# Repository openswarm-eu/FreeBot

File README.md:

# FreeBot
Contains FreeBot files and source code.
The Hardware folder contains schematics for the various versions of the FreeBot board and associated evaluation boards.
The software folder contains the FreeBot subfolder, which contains the core functionality of FreeBot and reference implementation of the library for BLE control. 
The repository will keep being updated with designs for both hardware and software.

# Hardware revisions

| Version        | SoC      | Feather-header | Picture                                       |
|:--------------:|:--------:|:--------------:|:---------------------------------------------:|
| [v1.0a](#v10a) | nrf52840 | &cross;        ||
| [v1.1a](#v11a) | nrf52840 | &cross;        ||
| [v1.1b](#v11b) | nrf52840 | &check;        ||

## v1.0a

CapBot v1.0 has a physical switch (`SW4`) to cut the UART lines from the DAP-link on-board debugger.
This switch should be enabled when printing to a serial terminal over USB.

Furthermore, another physical switch (`SW3`) cuts the SWD lines used for programming the &micro;Processor.
This switch should be enabled in order to flash.

## v1.1a

Nothing special (yet).

## v1.1b

> [!WARNING]
> The pins `IO1`, `IO2` and `IO3` on the feather-header correspond with `D15`, `D16` and `SW2` respectively.
> Make sure that these are not shorted accidentally because of this.
> 

# Acknowledgement

Part of the source code in this repository is developed within the frame and for the purpose of the OpenSwarm project. This project has received funding from the European Unioan's Horizon Europe Framework Programme under Grant Agreement No. 101093046.

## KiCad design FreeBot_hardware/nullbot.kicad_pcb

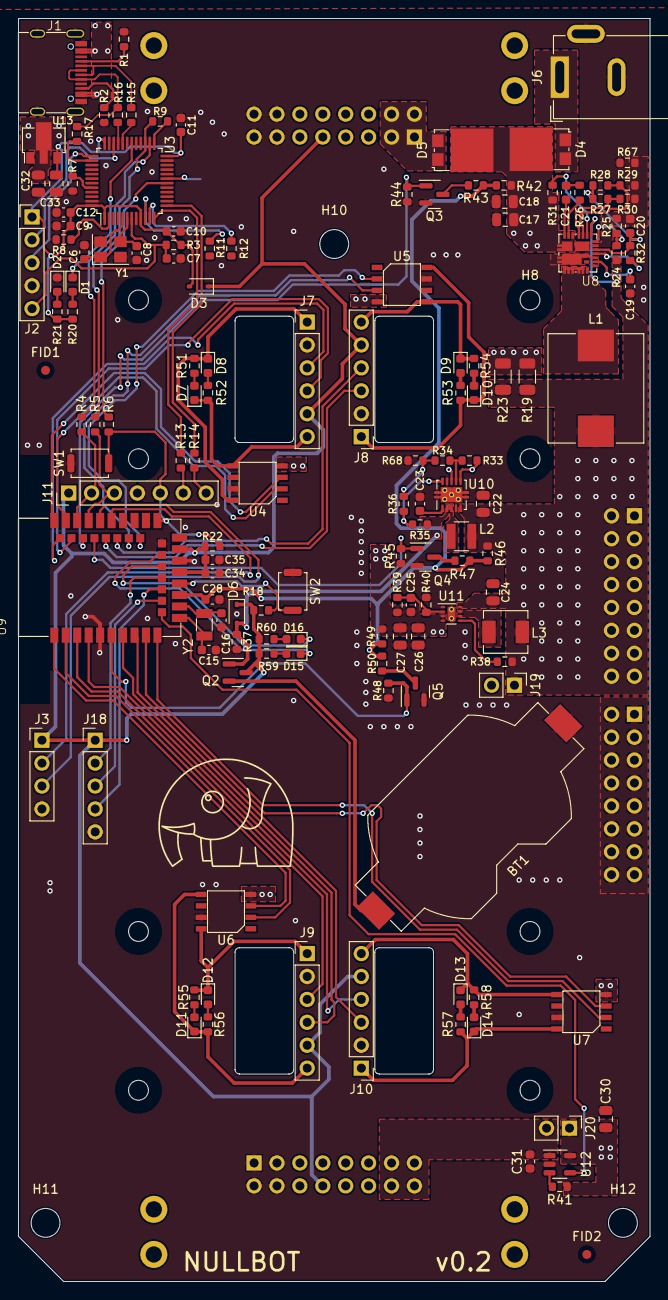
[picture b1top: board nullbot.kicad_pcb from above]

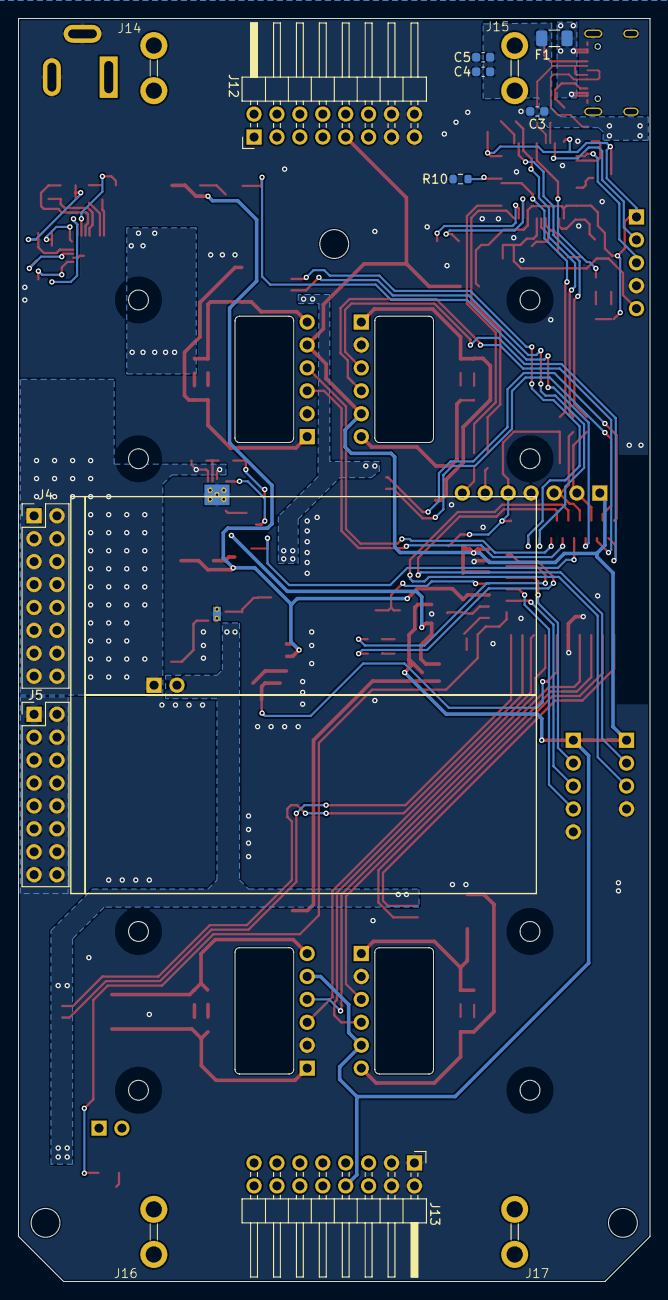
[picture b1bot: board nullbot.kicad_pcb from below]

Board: 2 copper layers, 70.0 x 140.0 mm, 165 parts (13 on the bottom side), 116 nets.

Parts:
BT1: Battery_Cell; BatteryHolder_Keystone_1058_1x2032
C3, C4, C5, C20: 1uF; C_0603_1608Metric
C6, C8: 22p; C_0603_1608Metric
C7, C9, C10, C11, C12: 100n; C_0603_1608Metric
C15, C16: 12pF; C_0603_1608Metric
C17, C18, C26, C27: 22uF; C_0805_2012Metric
C19: 2.2uF; C_0603_1608Metric
C21, C23, C31, C34, C35: 0.1uF; C_0603_1608Metric
C22, C24, C30, C32, C33: 10uF; C_0805_2012Metric
C25: 10pF; C_0603_1608Metric
C28: 0.01uF; C_0603_1608Metric
D1: Red; LED_0603_1608Metric
D2: Green; LED_0603_1608Metric
D3, D6: CUS10S30,H3F; D_SOD-323
D4, D5: 10S45SP; TO-277A
D7, D10, D11, D14: GREEN LED NCD0603G1; LED_0603_1608Metric
D8, D9, D12, D13: RED LED NCD0603R1; LED_0603_1608Metric
D15, D16: 19-217/BHC-ZL1M2RY/3T; LED_0603_1608Metric
F1: S1206-F-6.0A; Fuse_1206_3216Metric
FID1, FID2: Fiducial; Fiducial_1mm_Mask2mm
H1, H2, H3, H4, H5, H6, H7, H8: MountingHole; MountingHole_2.2mm_M2_ISO7380
H10, H11, H12: MountingHole; MountingHole_3.2mm_M3_ISO14580
J1: USB-type-c-16p; TYPE-C-31-M-12
J2, J18: Conn_01x05; PinHeader_1x05_P2.54mm_Vertical
J3: Conn_01x04; PinHeader_1x04_P2.54mm_Vertical
J4, J5: Conn_02x08_Counter_Clockwise; PinHeader_2x08_P2.54mm_Vertical
J6: Barrel_Jack_MountingPin; BarrelJack_GCT_DCJ200-10-A_Horizontal
J7, J8, J9, J10: Conn_01x06; PinHeader_1x06_P2.54mm_Vertical
J11: Conn_01x07; PinHeader_1x07_P2.54mm_Vertical
J12, J13: Conn_02x08_Odd_Even; PinHeader_2x08_P2.54mm_Horizontal
J14, J17: Conn_01x01; M3-side-terminal-DZ-32
J15, J16: Conn_01x01; M3-side-terminal-DZ-43
J19, J20: Conn_01x02; PinHeader_1x02_P2.54mm_Vertical
L1: 300nH; L_Chilisin_BMRF00101040
L2: 2.2uH SWPA3015S2R2MT; L_Abracon_ASPI-3012S
L3: 470nH FXL0420-R47-M; L_Sunlord_MWSA0412S
Q2: SSM3J332R; SOT-23
Q3, Q4, Q5: 2N7002; SOT-23
R1, R2: 5.1k; R_0603_1608Metric
R3, R7, R18, R22, R27, R31, R32, R38, R40, R41, R44, R45, R48: 100k; R_0603_1608Metric
R4, R5, R6, R11, R12, R13, R14, R15, R16: 22; R_0603_1608Metric
R8: 10k DNP; R_0603_1608Metric
R9, R20, R52, R53, R56, R57, R59, R60: 100; R_0603_1608Metric
R10, R68: 0; R_0603_1608Metric
R17: 1.5k; R_0603_1608Metric
R19, R23: DNP; R_1206_3216Metric
R21, R51, R54, R55, R58: 27; R_0603_1608Metric
R24: 36.5k; R_0603_1608Metric
R25, R34, R43, R47, R50: 10k; R_0603_1608Metric
R26, R67: 1; R_0603_1608Metric
R28: 499k; R_0603_1608Metric
R29, R30: DNP; R_0603_1608Metric
R33: 34.8k; R_0603_1608Metric
R35, R37: 1M; R_0603_1608Metric
R36: 180k; R_0603_1608Metric
R39: 316k; R_0603_1608Metric
R42, R46, R49: 390k; R_0603_1608Metric
SW1, SW2: TS-1088-AR02016; SW_Push_SPST_NO_Alps_SKRK
U3: STM32F103CBTx; LQFP-48_7x7mm_P0.5mm
U4, U5, U6, U7: BDR6120H; motor-driver-BDR6120H
U8: SIC431AED-T1-GE3; MLP44-24L SiC431
U9: E73-2G4M08S1C
U10: TPS61201DRC; Texas_S-PVSON-N10_ThermalVias
U11: WSON-8-1EP_2x2mm_P0.5mm_EP0.9x1.6mm_ThermalVias
U12: RT9742AGJ5F; TSOT-23-5
U13: HT7533-1; SOT-89-3
Y1: Crystal_GND24; Crystal_SMD_3225-4Pin_3.2x2.5mm
Y2: Q13FC1350000400; Crystal_SMD_3215-2Pin_3.2x1.5mm

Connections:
/USB-VDD: C9.1, C10.1, C11.1, C12.1, C33.1, D3.2 (A), J2.1, R3.2, R20.1, R21.1, U3.1 (VBAT), U3.9 (VDDA), U3.24 (VDD), U3.36 (VDD), U3.48 (VDD), U13.3 (VOUT)
/Vbotin: D5.1 (A), D5.2 (A), J12.1, J12.2, J12.3, J12.4
/Vbotout: C31.2, J13.13, J13.14, J13.15, J13.16, J20.2, U12.1 (VOUT)
/Vmotor: C25.2, C26.1, C27.1, C30.1, J19.2, J20.1, R39.1, R41.1, R49.1, U4.4 (VDD), U5.4 (VDD), U6.4 (VDD), U7.4 (VDD), U11.3 (VOUT), U11.4 (VOUT), U12.5 (VIN)
/daplink/dap-inner-usb_N: R15.2, U3.32 (PA11)
/daplink/dap-inner-usb_P: R16.2, U3.33 (PA12)
/daplink/dap-led-red: D1.1 (K), U3.30 (PA9)
/daplink/dap-nrst: C7.1, J2.5, R3.1, U3.7 (NRST)
/daplink/dap-swclk: J2.3, U3.37 (PA14)
/daplink/dap-swdio: J2.2, U3.34 (PA13)
/daplink/dap-usbd_N: J1.A7 (DN1), J1.B7 (DN2), R15.1
/daplink/dap-usbd_P: J1.A6 (DP1), J1.B6 (DP2), R16.1, R17.2
/daplink/tgt-swd.clk: J11.2, R4.1, U9.39 (SWDCLK)
/daplink/tgt-swd.io: J11.3, R5.1, U9.37 (SWDIO)
/daplink/tgt-swd.rst: J11.5, R6.1, R22.2, SW1.2, U9.26 (P0.18/RESET)
/daplink/tgt-uart.rx: J11.7, R14.2
/daplink/tgt-uart.tx: J11.6, R13.2
/mcu/V-mea: C28.1, R42.2, R43.1, R46.2, R47.1, R49.2, R50.1, U9.15 (P0.05/AIN3)
/mcu/Vbotout-EN: U9.12 (P0.26), U12.4 (EN)
/mcu/Vcap-mea-en: Q4.1 (G), R45.1, U9.36 (P1.00/SWO)
/mcu/Vin-mea-en: Q3.1 (G), R44.1, U9.38 (P1.02-LS)
/mcu/Vmotor-mea-en: Q5.1 (G), R48.1, U9.6 (P1.13-LS)
/mcu/m1-ctrl.in-a: U4.2 (INA), U9.41 (P0.09/NFC1-LS)
/mcu/m1-ctrl.in-b: U4.3 (INB), U9.43 (P0.10/NFC2-LS)
/mcu/m1-hall.c1: J7.4, U9.40 (P1.04-LS)
/mcu/m1-hall.c2: J7.3, U9.42 (P1.06-LS)
/mcu/m2-ctrl.in-a: U5.2 (INA), U9.28 (P0.15)
/mcu/m2-ctrl.in-b: U5.3 (INB), U9.30 (P0.17)
/mcu/m2-hall.c1: J8.4, U9.32 (P0.20)
/mcu/m2-hall.c2: J8.3, U9.34 (P0.22)
/mcu/m3-ctrl.in-a: U6.2 (INA), U9.2 (P1.10-LS)
/mcu/m3-ctrl.in-b: U6.3 (INB), U9.1 (P1.11-LS)
/mcu/m3-hall.c1: J9.4, U9.7 (P0.02/AIN1-LS)
/mcu/m3-hall.c2: J9.3, U9.3 (P0.03/AIN1-LS)
/mcu/m4-ctrl.in-a: U7.2 (INA), U9.10 (P0.30/AIN6-LS)
/mcu/m4-ctrl.in-b: U7.3 (INB), U9.9 (P0.31/AIN7-LS)
/mcu/m4-hall.c1: J10.4, U9.4 (P0.28/AIN4-LS)
/mcu/m4-hall.c2: J10.3, U9.8 (P0.29/AIN5-LS)
/mcu/nrf-led1: D15.1 (K), U9.22 (P0.07)
/mcu/nrf-led2: D16.1 (K), U9.20 (P0.12)
/mcu/nrf-sw: R18.2, SW2.2, U9.17 (P1.09)
/mcu/peri-i2c.scl: J3.3, U9.35 (P0.24)
/mcu/peri-i2c.sda: J3.2, U9.33 (P0.13)
/mcu/peri-spi.miso: J18.4, U9.16 (P0.08)
/mcu/peri-spi.mosi: J18.2, U9.18 (P0.04/AIN2)
/mcu/peri-spi.sck: J18.3, U9.14 (P0.06)
/pwr1/Vcap: C22.1, C24.1, J4.1, J4.2, J4.3, J4.4, J4.5, J4.6, J4.7, J4.8, J4.9, J4.10, J4.11, J4.12, J4.13, J4.14, J4.15, J4.16, J19.1, L1.2, L2.1, L3.1, R19.2, R23.2, R24.1, R33.1, R38.1, R46.1, U8.18 (Vout), U10.5 (VIN), U10.6 (EN), U10.8 (PS), U11.8 (VIN)
/pwr1/buck_en: R31.2, U8.19 (EN)
/pwr2/Vbotout-overcurr: R41.2, U12.3 (~FLG)
/pwr2/Vcap_reg: D6.2 (A), Q2.1 (G), R35.1, R37.1, U10.2 (VOUT)
/pwr2/Vmotor-EN: R38.2, U11.5 (EN)
GND: BT1.2 (-), C3.2, C4.2, C5.2, C6.2, C7.2, C8.2, C9.2, C10.2, C11.2, C12.2, C15.2, C16.2, C17.2, C18.2, C19.2, C20.2, C22.2, C23.1, C24.2, C26.2, C27.2, C28.2, C30.2, C31.1, C32.2, C33.2, C34.2, C35.2, D2.1 (K), J1.0 (SH), J1.1 (SH), J1.2 (SH), J1.3 (SH), J1.A1 (GND), J1.A12 (GND), J1.B1 (GND), J1.B12 (GND), J2.4, J3.4, J5.1, J5.2, J5.3, J5.4, J5.5, J5.6, J5.7, J5.8, J5.9, J5.10, J5.11, J5.12, J5.13, J5.14, J5.15, J5.16, J6.2, J6.3 (MP), J7.2, J8.2, J9.2, J10.2, J11.4, J12.13, J12.14, J12.15, J12.16, J13.1, J13.2, J13.3, J13.4, J18.5, Q3.2 (S), Q4.2 (S), Q5.2 (S), R1.2, R2.2, R7.2, R8.1, R10.1, R25.2, R29.2, R30.2, R37.2, R40.2, R44.2, R45.2, R48.2, R67.1, R67.2, R68.2, SW1.1, SW2.1, U3.8 (VSSA), U3.23 (VSS), U3.35 (VSS), U3.47 (VSS), U4.7 (GND), U5.7 (GND), U6.7 (GND), U7.7 (GND), U8.3 (Pgnd), U8.4 (Pgnd), U8.13 (Pgnd), U8.16 (Agnd), U8.25 (Agnd), U8.27 (Pgnd), U9.5 (GND), U9.21 (GND), U9.24 (GND), U10.4 (PGND), U10.9 (GND), U10.11 (PAD), U11.1 (AGND), U11.9 (PGND), U12.2 (GND), U13.1 (GND), Y1.2, Y1.4
unnamed: BT1.1 (+), Q2.2 (S)
unnamed: C21.2, R26.2
unnamed: D1.2 (A), R20.2
unnamed: D2.2 (A), R21.2
unnamed: D4.1 (A), D4.2 (A), J6.1
unnamed: C17.1, C18.1, D4.3 (K), D5.3 (K), R19.1, R23.1, R31.1, R42.1, U8.1 (Vin), U8.2 (Vin), U8.22 (Vin), U8.26 (Vin)
unnamed: D7.2 (A), R51.2
unnamed: D7.1 (K), J7.6, R52.2, U4.5 (OUTB)
unnamed: D8.2 (A), R52.1
unnamed: D8.1 (K), J7.1, R51.1, U4.8 (OUTA)
unnamed: D9.2 (A), R53.2
unnamed: D9.1 (K), J8.6, R54.2, U5.5 (OUTB)
unnamed: D10.2 (A), R54.1
unnamed: D10.1 (K), J8.1, R53.1, U5.8 (OUTA)
unnamed: D11.2 (A), R55.2
unnamed: D11.1 (K), J9.6, R56.2, U6.5 (OUTB)
unnamed: D12.2 (A), R56.1
unnamed: D12.1 (K), J9.1, R55.1, U6.8 (OUTA)
unnamed: D13.2 (A), R57.2
unnamed: D13.1 (K), J10.6, R58.2, U7.5 (OUTB)
unnamed: D14.2 (A), R58.1
unnamed: D14.1 (K), J10.1, R57.1, U7.8 (OUTA)
unnamed: D15.2 (A), R59.2
unnamed: D16.2 (A), R60.2
unnamed: F1.1, J1.A4 (VBUS), J1.A9 (VBUS), J1.B4 (VBUS), J1.B9 (VBUS)
unnamed: J1.A5 (CC1), R1.1
unnamed: J1.B5 (CC2), R2.1
unnamed: L1.1, U8.5 (SW), U8.6 (SW), U8.7 (SW), U8.8 (SW), U8.9 (SW)
unnamed: L3.2, U11.6 (SW), U11.7 (SW)
unnamed: Q3.3 (D), R43.2
unnamed: Q4.3 (D), R47.2
unnamed: Q5.3 (D), R50.2
unnamed: R34.2, R36.2, R68.1
unnamed: R7.1, U3.44 (BOOT0)
unnamed: R11.1, U3.10 (PA0)
unnamed: R12.1, U3.11 (PA1)
unnamed: R13.1, U3.12 (PA2)
unnamed: R14.1, U3.13 (PA3)
unnamed: R17.1, U3.38 (PA15)
unnamed: R6.2, U3.18 (PB0)
unnamed: R10.2, U3.19 (PB1)
unnamed: R9.2, U3.25 (PB12)
unnamed: R4.2, U3.26 (PB13)
unnamed: R5.2, R9.1, U3.27 (PB14)
unnamed: R8.2, U3.2 (PC13)
unnamed: C6.1, U3.5 (PD0), Y1.1
unnamed: C8.1, U3.6 (PD1), Y1.3
unnamed: R26.1, U8.23 (BOOT)
unnamed: R24.2, R25.1, U8.17 (FB)
unnamed: R27.2, R30.1, U8.21 (MODE1)
unnamed: R28.2, R29.1, U8.20 (MODE2)
unnamed: C21.1, U8.24 (PHASE)
unnamed: R32.2, U8.14 (Pgood)
unnamed: C20.1, R27.1, R28.1, R32.1, U8.15 (Vdd)
unnamed: C19.1, U8.12 (Vdrv)
unnamed: C15.1, U9.11 (P0.00/XL1), Y2.1
unnamed: C16.1, U9.13 (P0.01/XL2), Y2.2
unnamed: R35.2, R36.1, U10.10 (FB)
unnamed: L2.2, U10.3 (L)
unnamed: R33.2, R34.1, U10.7 (UVLO)
unnamed: C23.2, U10.1 (VAUX)
unnamed: C25.1, R39.2, R40.1, U11.2 (FB)
VBUS: C3.1, C4.1, C5.1, C32.1, F1.2, U13.2 (VIN)
VDD: C34.1, C35.1, D3.1 (K), D6.1 (K), J3.1, J7.5, J8.5, J9.5, J10.5, J11.1, J12.9, J13.8, J18.1, Q2.3 (D), R18.1, R22.1, R59.1, R60.1, U9.19 (VDD), U9.23 (VDDH)

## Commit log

2023-10-11 Create FreeBot_Hardware
2023-10-11 Create directory
2023-10-11 Rename FreeBot_Hardware to FreeBotv0
2023-10-11 Create FreeBotv0
2023-10-11 Rename directory to Others/Assemmbly
2023-10-11 Rename FreeBotv0 to FreeBot_Software/README.md
2023-11-14 Create Sensysdemo
2025-02-03 Add the all capbot main&bumper&cap zip
2025-02-03 Update README.md
    update the different versions of freebot
2025-10-01 readme: adding ack
